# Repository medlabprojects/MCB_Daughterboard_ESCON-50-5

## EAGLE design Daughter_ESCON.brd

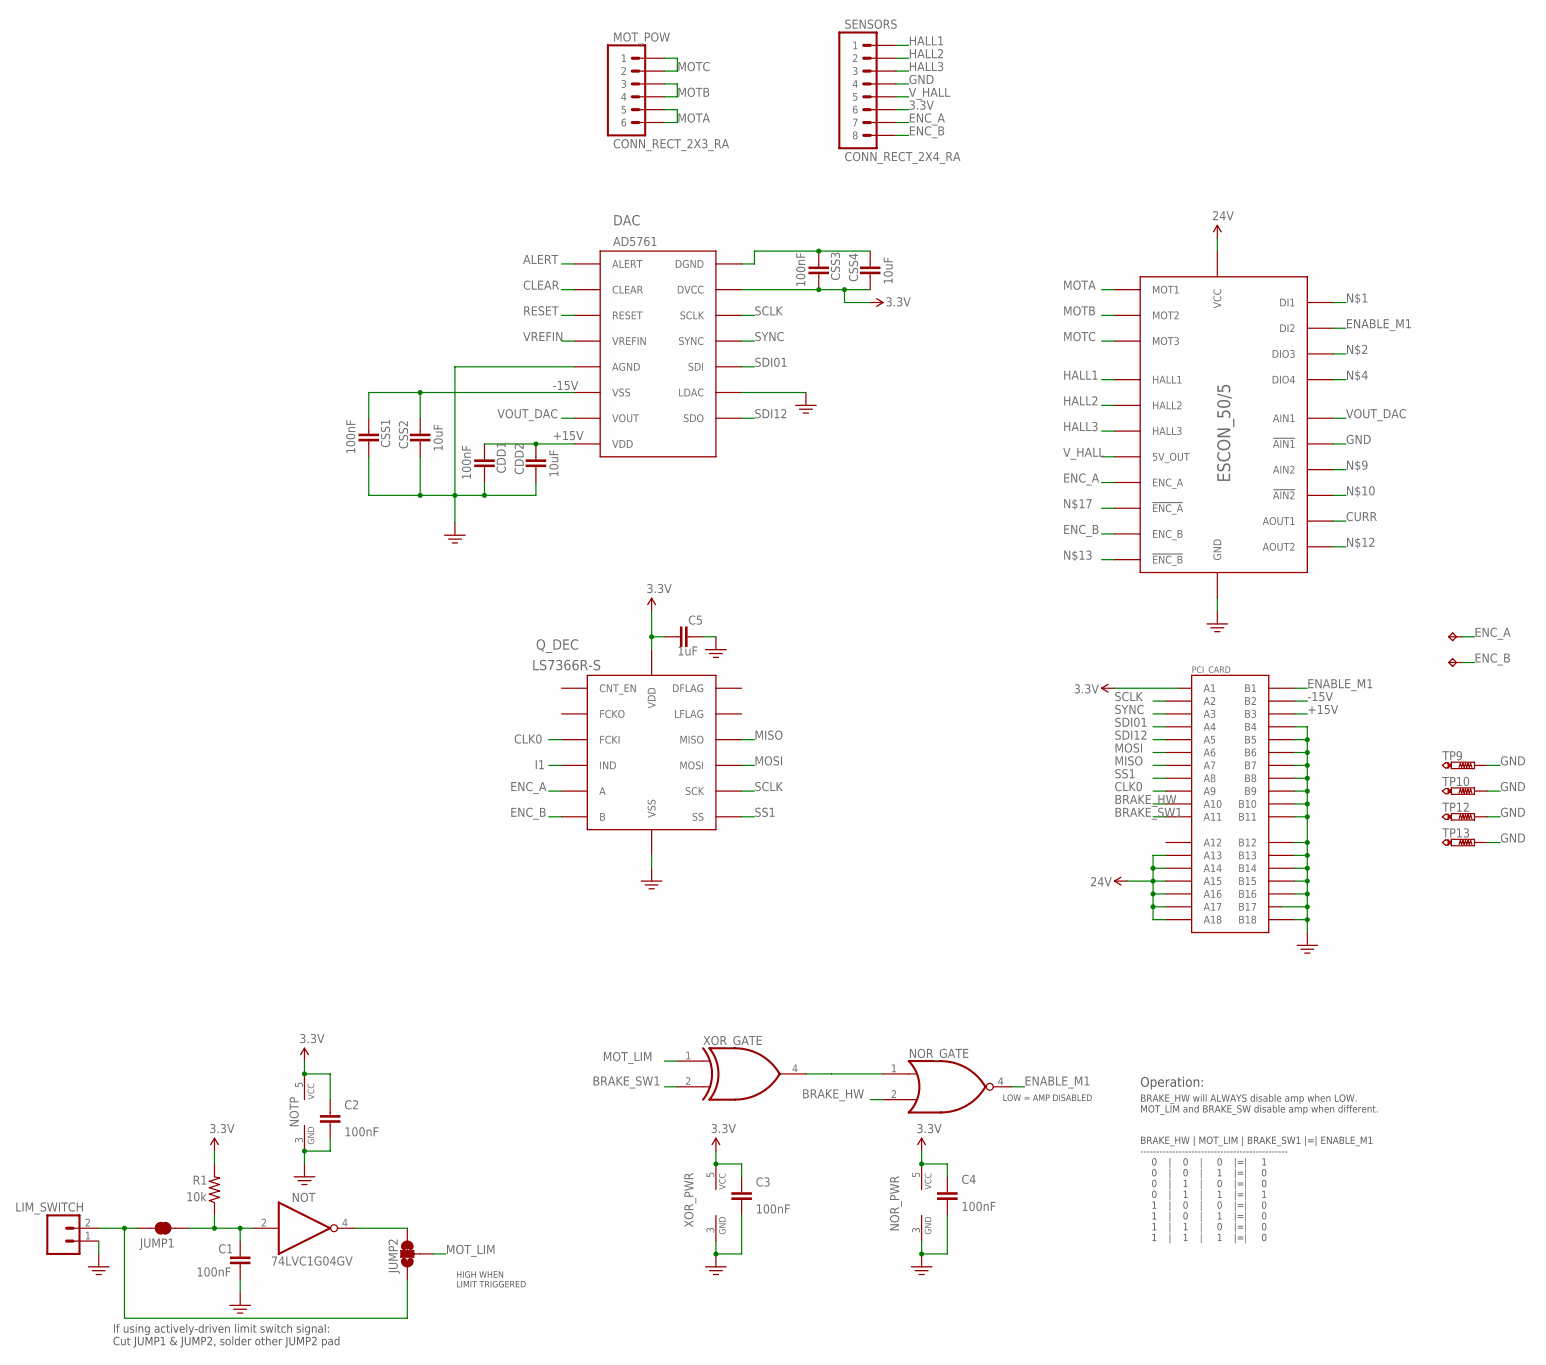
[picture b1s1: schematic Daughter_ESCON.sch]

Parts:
A: TEST_POINT_0805; 0805-TP
B: TEST_POINT_0805; 0805-TP
C1, C2, C3, C4: 100nF; 0603-CAP
C5: 1uF; 0603-CAP
CDD1: 100nF; 0603-CAP
CDD2: 10uF; C0805K
CSS1, CSS3: 100nF; 0603-CAP
CSS2, CSS4: 10uF; C0805K
DAC: AD5761; TSSOP16
ESCON_50/5: ESCON_50-5
JUMP1: JUMPER-PAD-2-NC_BY_TRACE; PAD-JUMPER-2-NC_BY_TRACE_YES_SILK
JUMP2: JUMPER-PAD-3-2OF3_NC_BY_TRACE; PAD-JUMPER-3-2OF3_NC_BY_TRACE_YES_SILK_FULL_BOX
LIM_SWITCH: 22-05-7028-02; 7395-02
MOT_POW: CONN_RECT_2X3_RA; 2X3-RA
NOR: NOR-SOT353; SOT353
NOT: 74LVC1G04GV; SOT23-5
PCI_CARD: PCIE-36-EDGE
Q_DEC: LS7366R-S; SOIC-14
R1: 10k; 0603-RES
SENSORS: CONN_RECT_2X4_RA; 2X4-RA
TP9, TP10, TP12, TP13: PTR1TP20R; TP20R
XOR: XOR-SOT353; SOT353

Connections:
3.3V: C2.1, C3.1, C4.1, C5.1, CSS3.2, CSS4.2, DAC.15 (DVCC), NOR.5 (VCC), NOT.5 (VCC), PCI_CARD.A1, Q_DEC.14 (VDD), R1.2, SENSORS.6, XOR.5 (VCC)
24V: ESCON_50/5.P$7 (VCC), ESCON_50/5.P$8 (VCC), PCI_CARD.A13, PCI_CARD.A14, PCI_CARD.A15, PCI_CARD.A16, PCI_CARD.A17, PCI_CARD.A18
+15V: CDD1.1, CDD2.1, DAC.8 (VDD), PCI_CARD.B3
-15V: CSS1.1, CSS2.1, DAC.6 (VSS), PCI_CARD.B2
ALERT: DAC.1 (ALERT)
BRAKE_HW: NOR.2 (B), PCI_CARD.A10
BRAKE_SW1: PCI_CARD.A11, XOR.2 (B)
CLEAR: DAC.2 (CLEAR)
CLK0: PCI_CARD.A9, Q_DEC.2 (FCKI)
CURR: ESCON_50/5.P$25 (AOUT1)
ENABLE_M1: ESCON_50/5.P$21 (DI2), NOR.4 (Y), PCI_CARD.B1
ENC_A: A.1, ESCON_50/5.P$12 (ENC_A), Q_DEC.12 (A), SENSORS.7
ENC_B: B.1, ESCON_50/5.P$16 (ENC_B), Q_DEC.11 (B), SENSORS.8
GND: C1.2, C2.2, C3.2, C4.2, C5.2, CDD1.2, CDD2.2, CSS1.2, CSS2.2, CSS3.1, CSS4.1, DAC.5 (AGND), DAC.11 (LDAC), DAC.16 (DGND), ESCON_50/5.P$9 (GND), ESCON_50/5.P$10 (GND), ESCON_50/5.P$23 (GND), ESCON_50/5.P$28 (!AIN1), LIM_SWITCH.1, NOR.3 (GND), NOT.3 (GND), PCI_CARD.B4, PCI_CARD.B5, PCI_CARD.B6, PCI_CARD.B7, PCI_CARD.B8, PCI_CARD.B9, PCI_CARD.B10, PCI_CARD.B11, PCI_CARD.B12, PCI_CARD.B13, PCI_CARD.B14, PCI_CARD.B15, PCI_CARD.B16, PCI_CARD.B17, PCI_CARD.B18, Q_DEC.3 (VSS), SENSORS.4, TP9.TP, TP10.TP, TP12.TP, TP13.TP, XOR.3 (GND)
HALL1: ESCON_50/5.P$13 (HALL1), SENSORS.1
HALL2: ESCON_50/5.P$15 (HALL2), SENSORS.2
HALL3: ESCON_50/5.P$17 (HALL3), SENSORS.3
I1: Q_DEC.10 (IND)
MISO: PCI_CARD.A7, Q_DEC.6 (MISO)
MOSI: PCI_CARD.A6, Q_DEC.7 (MOSI)
MOTA: ESCON_50/5.P$1 (MOT1), ESCON_50/5.P$2 (MOT1), MOT_POW.5, MOT_POW.6
MOTB: ESCON_50/5.P$3 (MOT2), ESCON_50/5.P$4 (MOT2), MOT_POW.3, MOT_POW.4
MOTC: ESCON_50/5.P$5 (MOT3), ESCON_50/5.P$6 (MOT3), MOT_POW.1, MOT_POW.2
MOT_LIM: JUMP2.2, XOR.1 (A)
unnamed: JUMP1.1, JUMP2.1, LIM_SWITCH.2
unnamed: C1.1, JUMP1.2, NOT.2 (I), R1.1
unnamed: JUMP2.3, NOT.4 (O)
unnamed: NOR.1 (A), XOR.4 (Y)
RESET: DAC.3 (RESET)
SCLK: DAC.14 (SCLK), PCI_CARD.A2, Q_DEC.5 (SCK)
SDI01: DAC.12 (SDI), PCI_CARD.A4
SDI12: DAC.10 (SDO), PCI_CARD.A5
SS1: PCI_CARD.A8, Q_DEC.4 (SS)
SYNC: DAC.13 (SYNC), PCI_CARD.A3
VOUT_DAC: DAC.7 (VOUT), ESCON_50/5.P$29 (AIN1)
VREFIN: DAC.4 (VREFIN)
V_HALL: ESCON_50/5.P$11 (5V_OUT), SENSORS.5

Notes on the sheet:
HIGH WHEN LIMIT TRIGGERED
LOW = AMP DISABLED
Operation:
BRAKE_HW will ALWAYS disable amp when LOW. MOT_LIM and BRAKE_SW disable amp when different.
BRAKE_HW | MOT_LIM | BRAKE_SW1 |=| ENABLE_M1 ---------------------------------------------- 0 | 0 | 0 |=| 1 0 | 0 | 1 |=| 0 0 | 1 | 0 |=| 0 0 | 1 | 1 |=| 1 1 | 0 | 0 |=| 0 1 | 0 | 1 |=| 0 1 | 1 | 0 |=| 0 1 | 1 | 1 |=| 0
If using actively-driven limit switch signal: Cut JUMP1 & JUMP2, solder other JUMP2 pad

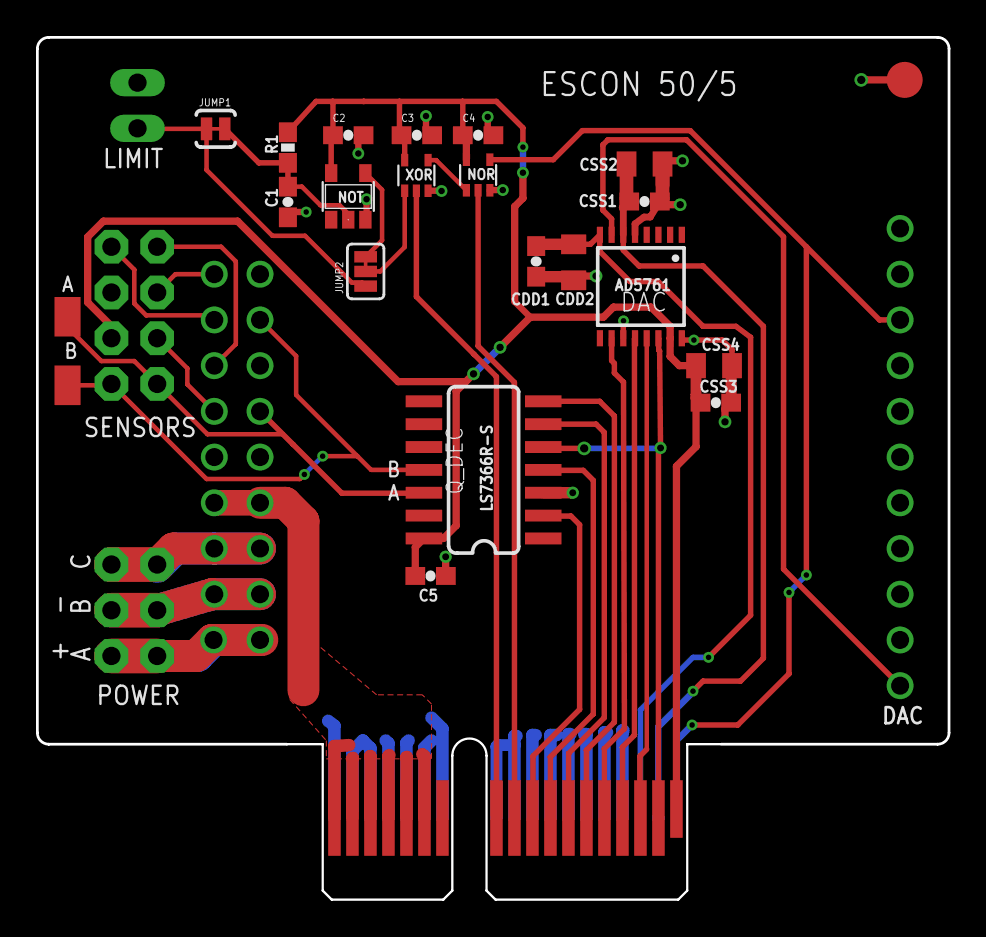
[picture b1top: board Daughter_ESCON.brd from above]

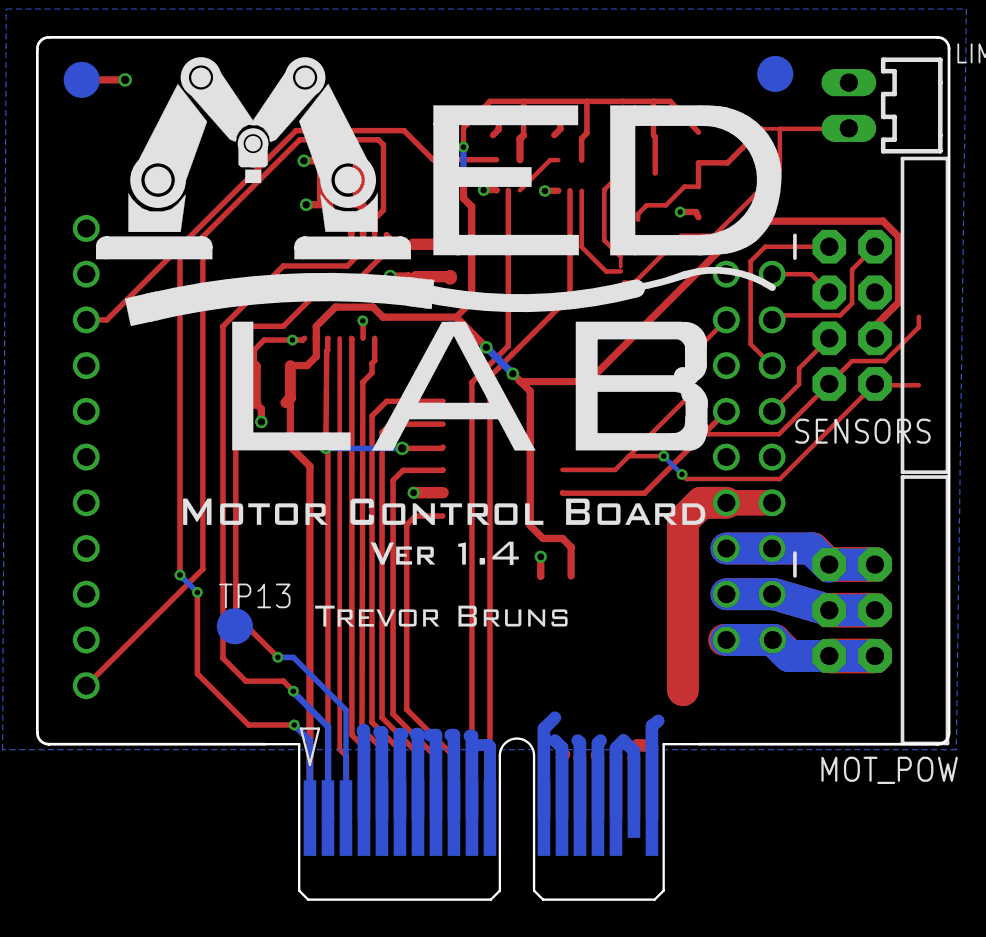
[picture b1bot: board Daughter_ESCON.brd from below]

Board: 2 copper layers, 50.6 x 47.9 mm, 32 parts (10 on the bottom side), 31 nets.

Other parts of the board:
U$2: LOGO_MOTOR_CONTROL_1.4_SMALL
U$6: LOGO_MEDLAB_1.5X0.86

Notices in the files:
parts and their libraries:
SparkFun-Capacitors: Licensing: Creative Commons ShareAlike 4.0 International - https://creativecommons.org/licenses/by-sa/4.0
